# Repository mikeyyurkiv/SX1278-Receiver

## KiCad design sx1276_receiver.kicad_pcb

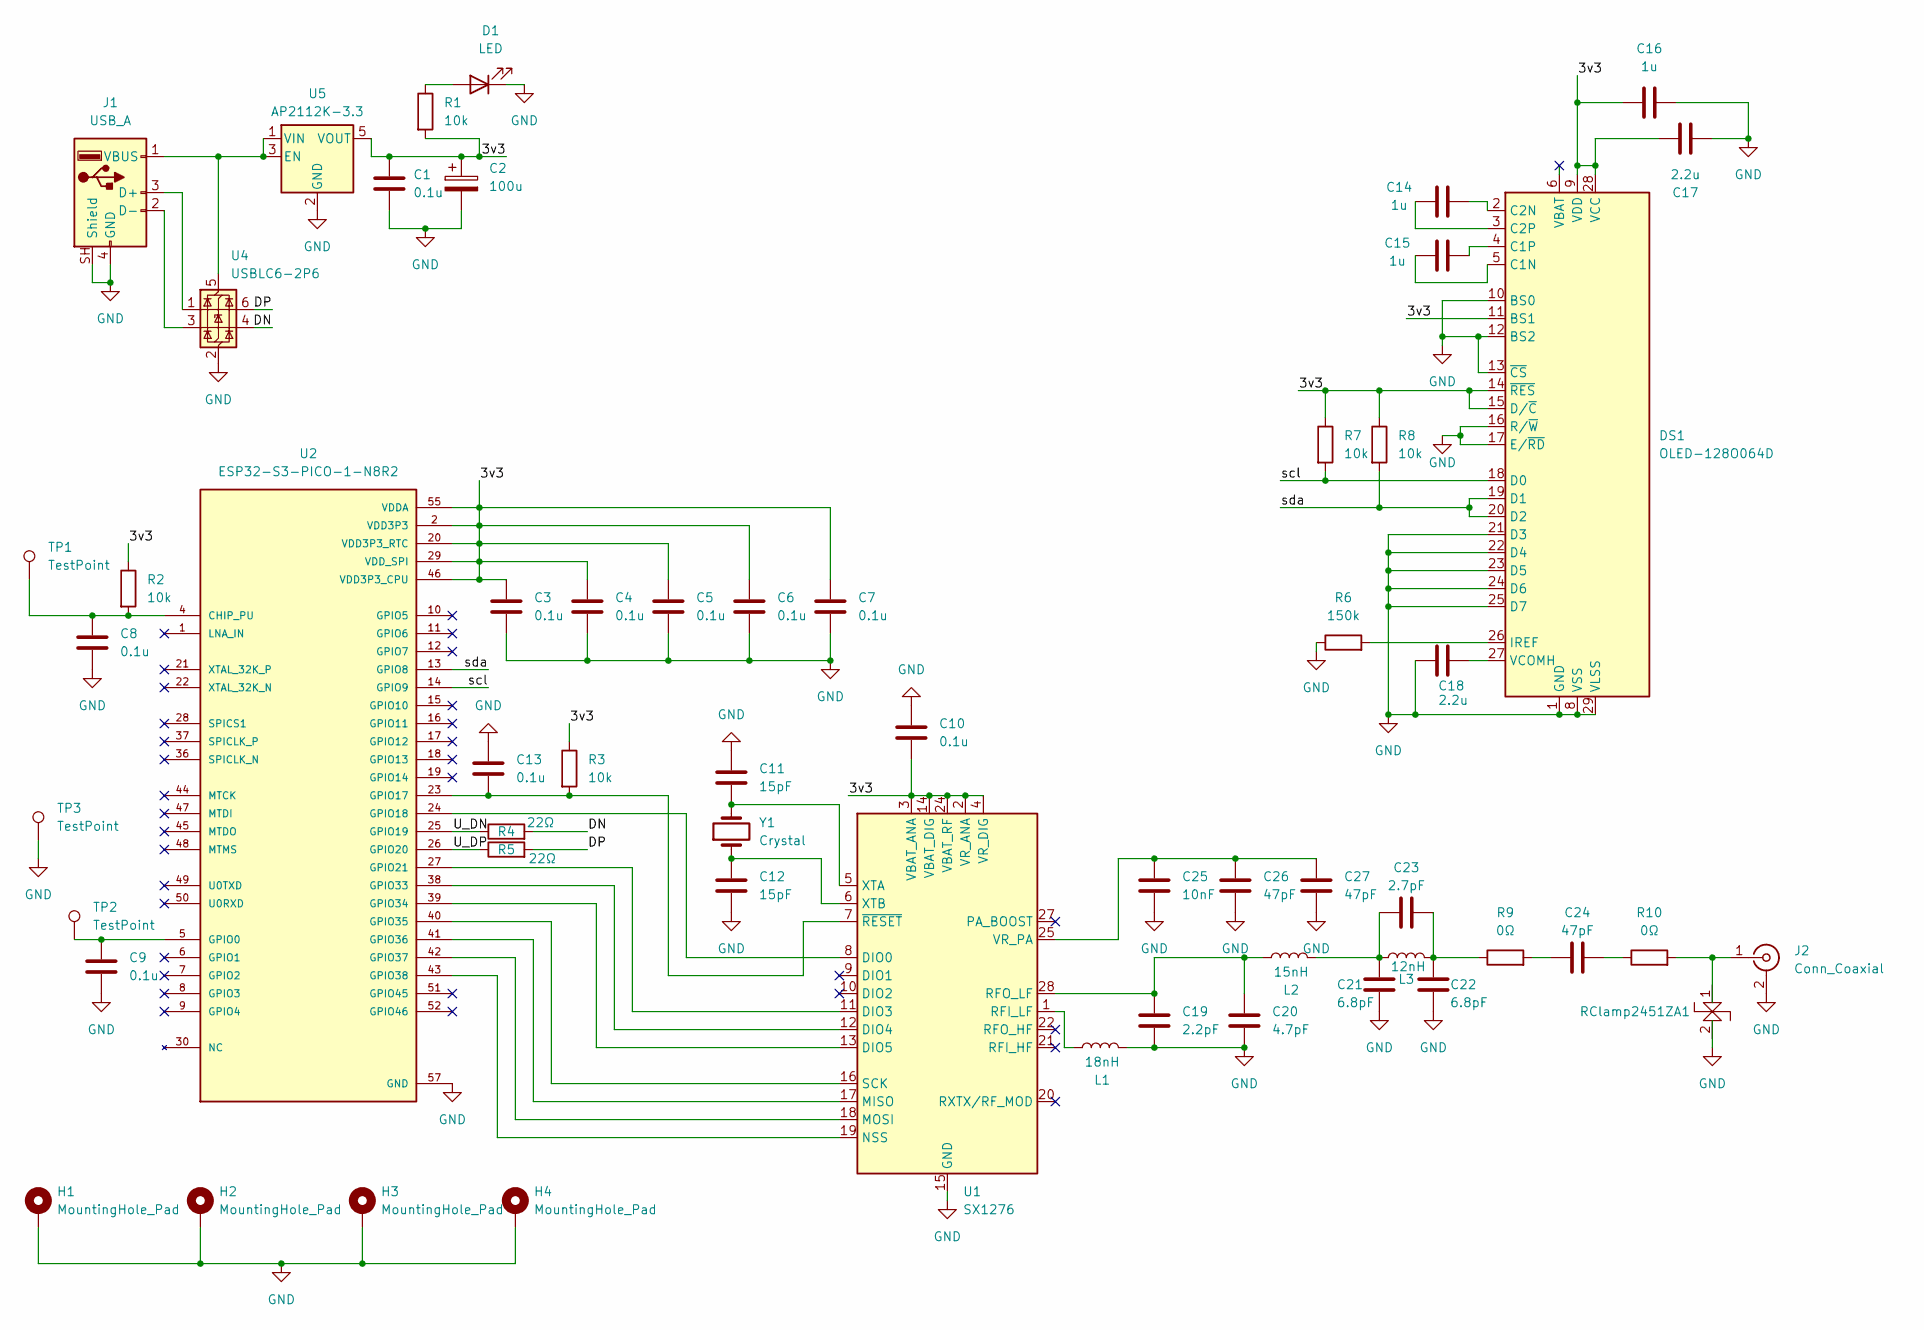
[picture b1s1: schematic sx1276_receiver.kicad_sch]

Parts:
C1, C3, C4, C5, C6, C7, C8, C9, C10, C13: 0.1u; C_0603_1608Metric_Pad1.08x0.95mm_HandSolder
C2: 100u; CP_EIA-2012-15_AVX-P_HandSolder
C11, C12: 15pF; C_0402_1005Metric_Pad0.74x0.62mm_HandSolder
C14, C15, C16: 1u; C_0603_1608Metric_Pad1.08x0.95mm_HandSolder
C17, C18: 2.2u; C_0603_1608Metric_Pad1.08x0.95mm_HandSolder
C19: 2.2pF; C_0402_1005Metric_Pad0.74x0.62mm_HandSolder
C20: 4.7pF; C_0402_1005Metric_Pad0.74x0.62mm_HandSolder
C21, C22: 6.8pF; C_0402_1005Metric_Pad0.74x0.62mm_HandSolder
C23: 2.7pF; C_0402_1005Metric_Pad0.74x0.62mm_HandSolder
C24, C26, C27: 47pF; C_0402_1005Metric_Pad0.74x0.62mm_HandSolder
C25: 10nF; C_0402_1005Metric_Pad0.74x0.62mm_HandSolder
D1: LED; LED_0603_1608Metric_Pad1.05x0.95mm_HandSolder
DS1: OLED-128O064D
H1, H2, H3, H4: MountingHole_Pad; MountingHole_2.2mm_M2
J1: USB_A; USB_A-custom
J2: Conn_Coaxial; SMA_Samtec_SMA-J-P-H-ST-EM1_EdgeMount
L1: 18nH; L_0402_1005Metric_Pad0.77x0.64mm_HandSolder
L2: 15nH; L_0402_1005Metric_Pad0.77x0.64mm_HandSolder
L3: 12nH; L_0402_1005Metric_Pad0.77x0.64mm_HandSolder
R1, R2, R3, R7, R8: 10k; R_0603_1608Metric_Pad0.98x0.95mm_HandSolder
R4, R5: 22Ω; R_0603_1608Metric_Pad0.98x0.95mm_HandSolder
R6: 150k; R_0603_1608Metric_Pad0.98x0.95mm_HandSolder
R9, R10: 0Ω; R_0402_1005Metric_Pad0.72x0.64mm_HandSolder
RClamp2451ZA1: D_0201_0603Metric_Pad0.64x0.40mm_HandSolder
TP1, TP2, TP3: TestPoint; TestPoint_THTPad_D1.5mm_Drill0.7mm
U1: SX1276; QFN-28-1EP_6x6mm_P0.65mm_EP4.8x4.8mm
U2: ESP32-S3-PICO-1-N8R2; PQFN40P700X700X106-57N; PARTREV 1.0
U4: USBLC6-2P6; SOT-666
U5: AP2112K-3.3; SOT-23-5
Y1: Crystal; Crystal_SMD_2016-4Pin_2.0x1.6mm

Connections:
/DN: R4.2, U4.4 (I/O2)
/DP: R5.2, U4.6 (I/O1)
/U_DN: R4.1, U2.25 (GPIO19)
/U_DP: R5.1, U2.26 (GPIO20)
/scl: DS1.18 (D0), R7.2, U2.14 (GPIO9)
/sda: DS1.19 (D1), DS1.20 (D2), R8.2, U2.13 (GPIO8)
GND: C1.2, C2.2, C3.1, C4.1, C5.1, C6.1, C7.1, C8.1, C9.1, C10.2, C11.2, C12.1, C13.2, C16.2, C17.1, C18.1, C19.1, C20.1, C21.1, C22.1, C25.1, C26.1, C27.1, D1.1 (K), DS1.1 (GND), DS1.8 (VSS), DS1.10 (BS0), DS1.12 (BS2), DS1.13 (~CS), DS1.16 (R/~W), DS1.17 (E/~RD), DS1.21 (D3), DS1.22 (D4), DS1.23 (D5), DS1.24 (D6), DS1.25 (D7), DS1.29 (VLSS), DS1.30 (GND), H1.1, H2.1, H3.1, H4.1, J1.4 (GND), J1.SH (Shield), J2.2 (Ext), L1.2, R6.1, RClamp2451ZA1.2, TP3.1 (1_1), U1.15 (GND), U1.23 (GND), U1.26 (GND), U1.29 (GND), U2.57 (GND), U4.2 (GND), U5.2 (GND)
unnamed: C21.2, C23.2, L2.2, L3.1
unnamed: C22.2, C23.1, L3.2, R9.1
unnamed: C24.1, R10.1
unnamed: C24.2, R9.2
unnamed: D1.2 (A), R1.1
unnamed: C15.2, DS1.5 (C1N)
unnamed: C15.1, DS1.4 (C1P)
unnamed: C14.1, DS1.2 (C2N)
unnamed: C14.2, DS1.3 (C2P)
unnamed: DS1.26 (IREF), R6.2
unnamed: C18.2, DS1.27 (VCOMH)
unnamed: J1.3 (D+), U4.1 (I/O1)
unnamed: J1.2 (D-), U4.3 (I/O2)
unnamed: J1.1 (VBUS), U4.5 (VBUS), U5.1 (VIN), U5.3 (EN)
unnamed: J2.1 (In), R10.2, RClamp2451ZA1.1
unnamed: U1.8 (DIO0), U2.24 (GPIO18)
unnamed: U1.11 (DIO3), U2.27 (GPIO21)
unnamed: U1.12 (DIO4), U2.38 (GPIO33)
unnamed: U1.13 (DIO5), U2.39 (GPIO34)
unnamed: U1.17 (MISO), U2.41 (GPIO36)
unnamed: U1.18 (MOSI), U2.42 (GPIO37)
unnamed: U1.19 (NSS), U2.43 (GPIO38)
unnamed: L1.1, U1.1 (RFI_LF)
unnamed: C19.2, C20.2, L2.1, U1.28 (RFO_LF)
unnamed: U1.16 (SCK), U2.40 (GPIO35)
unnamed: C25.2, C26.2, C27.2, U1.25 (VR_PA)
unnamed: C11.1, U1.5 (XTA), Y1.2
unnamed: C12.2, U1.6 (XTB), Y1.1
unnamed: C13.1, R3.2, U1.7 (~RESET), U2.23 (GPIO17)
unnamed: C8.2, R2.2, TP1.1 (1_1), U2.4 (CHIP_PU)
unnamed: C9.2, TP2.1 (1_1), U2.5 (GPIO0)
VDD3P3: C1.1, C2.1, C3.2, C4.2, C5.2, C6.2, C7.2, C10.1, C16.1, C17.2, DS1.9 (VDD), DS1.11 (BS1), DS1.14 (~RES), DS1.15 (D/~C), DS1.28 (VCC), R1.2, R2.1, R3.1, R7.1, R8.1, U1.2 (VR_ANA), U1.3 (VBAT_ANA), U1.4 (VR_DIG), U1.14 (VBAT_DIG), U1.24 (VBAT_RF), U2.2 (VDD3P3), U2.3 (VDD3P3), U2.20 (VDD3P3_RTC), U2.29 (VDD_SPI), U2.46 (VDD3P3_CPU), U2.55 (VDDA), U2.56 (VDDA), U5.5 (VOUT)

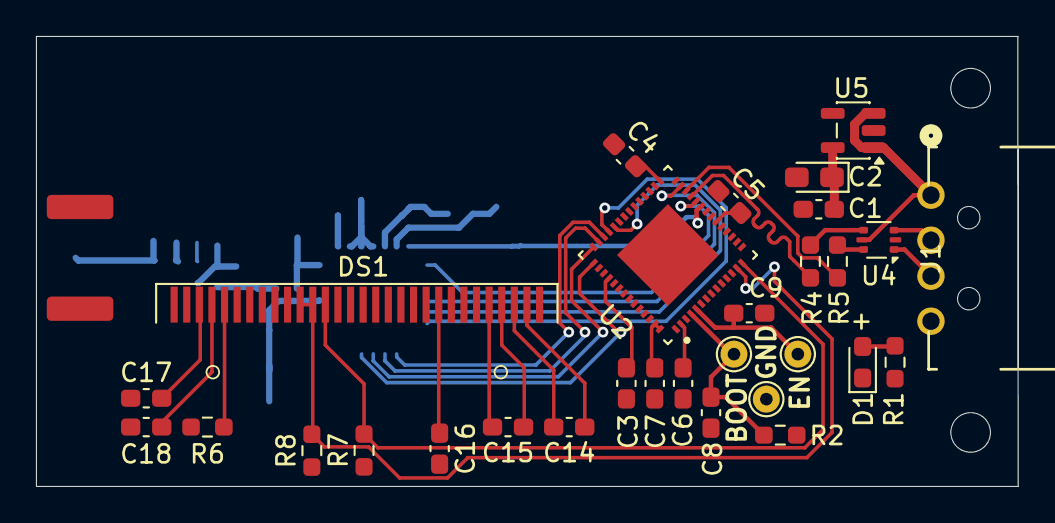
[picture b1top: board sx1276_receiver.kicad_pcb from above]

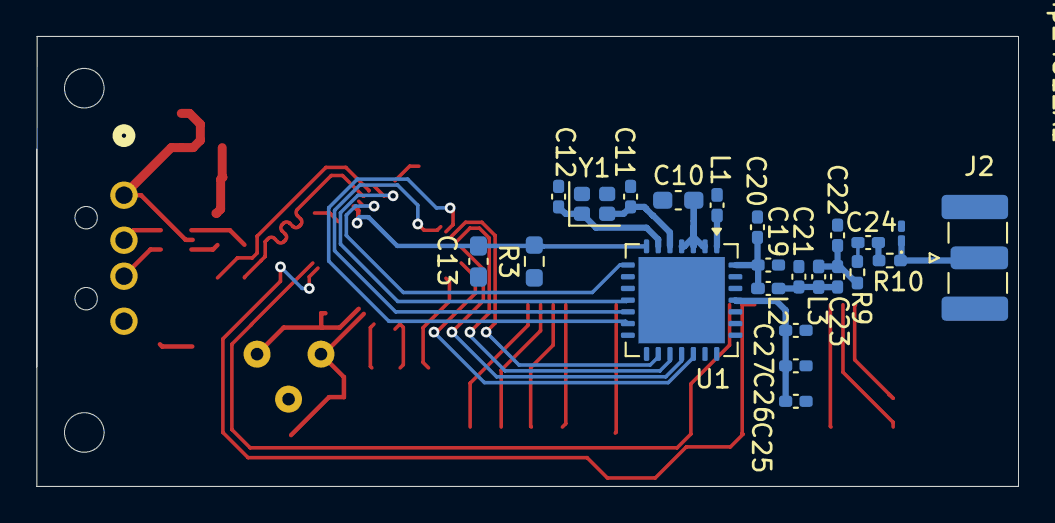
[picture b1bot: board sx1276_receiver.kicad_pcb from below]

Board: 4 copper layers, 54.6 x 25.0 mm, 57 parts (23 on the bottom side), 39 nets.

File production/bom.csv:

Designator,Footprint,Quantity,Value,LCSC Part #
"C1, C10, C13, C3, C4, C5, C6, C7, C8, C9",0603,10,0.1u,
"C11, C12",0402,2,15pF,
"C14, C15, C16",0603,3,1u,
"C17, C18",0603,2,2.2u,
C19,0402,1,2.2pF,
C2,CP_EIA-2012-15_AVX-P_HandSolder,1,100u,
C20,0402,1,4.7pF,
"C21, C22",0402,2,6.8pF,
C23,0402,1,2.7pF,
C24,0402,1,47pF,
D1,0603,1,LED,
DS1,OLED-128O064D,1,OLED-128O064D,
J1,USB_A-custom,1,USB_A,
J2,SMA_Samtec_SMA-J-P-H-ST-EM1_EdgeMount,1,Conn_Coaxial,
L1,0402,1,18nH,
L2,0402,1,15nH,
L3,0402,1,12nH,
"R1, R2, R3, R7, R8",0603,5,10k,
"R10, R9",0402,2,0Ω,
"R4, R5",0603,2,22Ω,
R6,0603,1,150k,
RCLAMP2451ZA1,0201,1,~,
"TP1, TP2, TP3",TestPoint_THTPad_D1.5mm_Drill0.7mm,3,TestPoint,
U1,QFN-28-1EP_6x6mm_P0.65mm_EP4.8x4.8mm,1,SX1276,
U2,PQFN40P700X700X106-57N,1,ESP32-S3-PICO-1-N8R2,
U4,SOT-666,1,USBLC6-2P6,
U5,SOT-23-5,1,AP2112K-3.3,
Y1,Crystal_SMD_2016-4Pin_2.0x1.6mm,1,Crystal,
